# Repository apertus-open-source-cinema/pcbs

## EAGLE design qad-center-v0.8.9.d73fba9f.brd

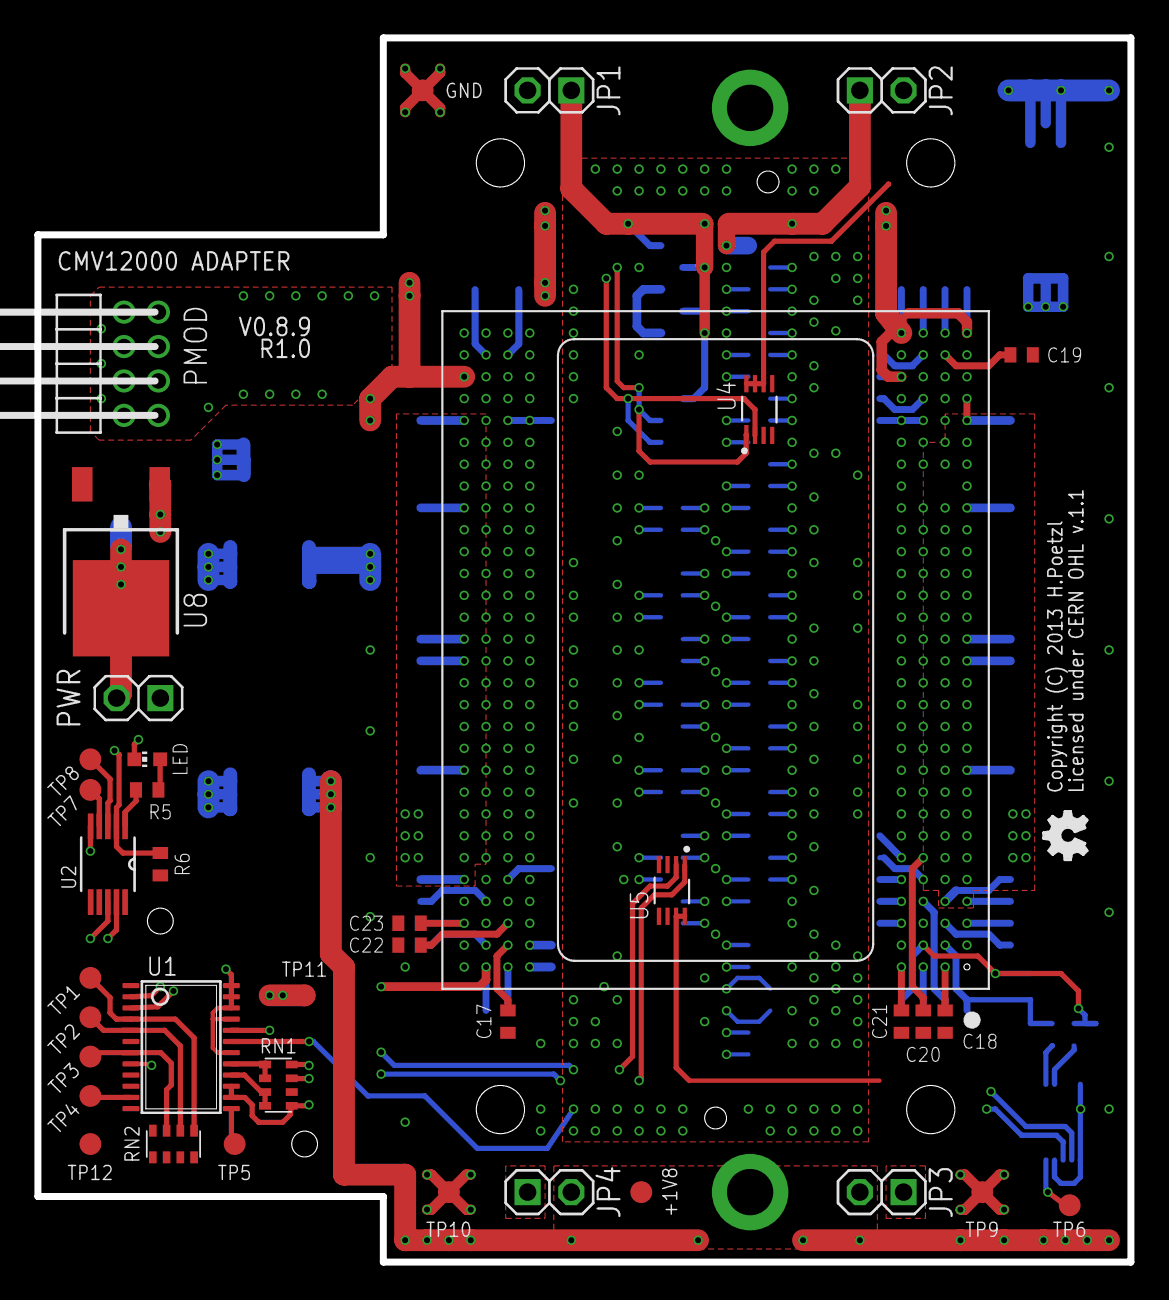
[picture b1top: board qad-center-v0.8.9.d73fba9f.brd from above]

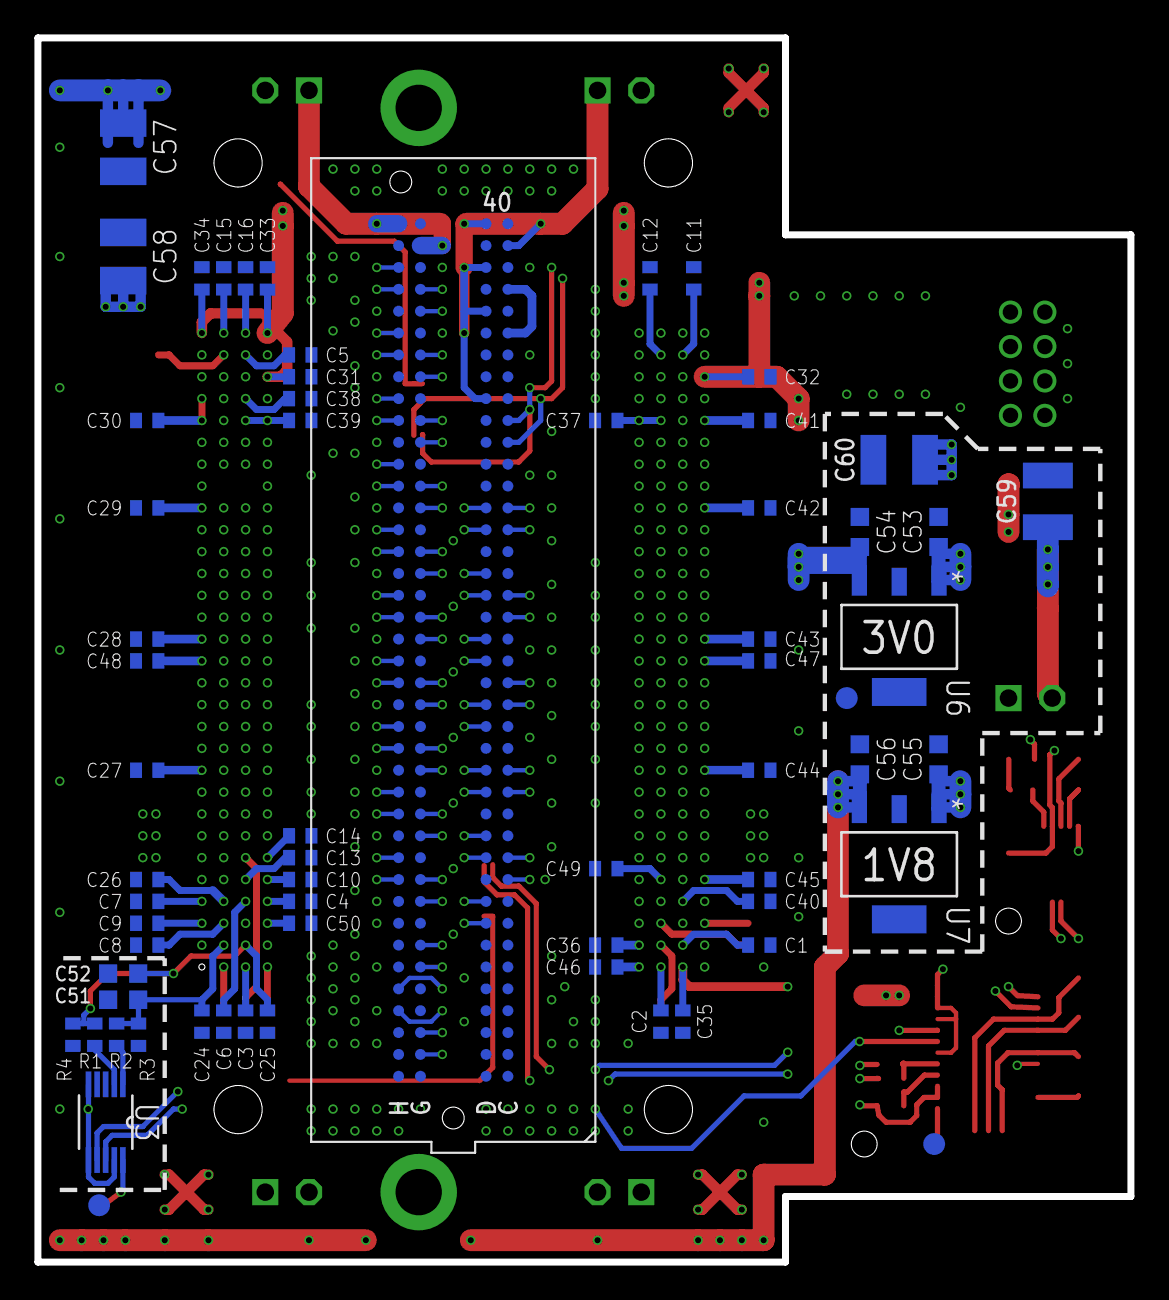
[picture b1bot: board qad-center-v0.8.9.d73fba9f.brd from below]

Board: 4 copper layers, 63.5 x 71.1 mm, 103 parts (63 on the bottom side), 130 nets.

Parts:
+1V8: TPB1,27; B1,27
C1, C2, C3, C4, C5, C6, C7, C8, C9, C10, C11, C12, C13, C14, C15, C16, C17, C18, C19, C20, C21, C22, C23, C24, C25, C26, C27, C28, C29, C30, C31, C32, C33, C34, C35, C36, C37, C38, C39, C40, C41, C42, C43, C44, C45, C46, C47, C48, C49, C50: 100n; C0402
C51, C52, C53, C54, C55, C56: 10u; C0603K
C57, C58: 100u; C1210
C59, C60: 100u; C1210K
GND: TPB1,27; B1,27
GND*1, GND*2, GND*3: TPB1,27; B1,27
JP1, JP2, JP3, JP4: 1X02-S
LED: RED; CHIP-LED0603
PMOD: PMOD-8; 2X04/90/2MM
PWR: 1X02-S
R1, R2: 1R; R0402
R3, R4: R0402
R5: 220R; R0402
R6: 10k; R0402
RN1, RN2: 10k; EXBV8V
TP1, TP2, TP3, TP4, TP5, TP6, TP7, TP8, TP9, TP10, TP11, TP12: TPB1,27; B1,27
U1: LM96080; TSSOP24
U2: PCA9537; TSSOP-10
U3: AD5647R; SOP50P490X110-10N
U4, U5: LM75BGD; SOT996-2/3
U6: MCP1826S-3002E/DB; SOT230P700X180-4N
U7: MCP1826S-1802E/DB; SOT230P700X180-4N
U8: AP1084TO252; TO252
U$1: CMV12000ANDON+LM; 10-30-07-237-400T4+LM
U$5: OSHW_FILLX100_NOTEXT
ZED1: FMC-LPC-ZED_NOCCZED; ASP-134604-01-ZED

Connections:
+1V8: +1V8.TP, C56.1, C57.1, JP2.2, JP3.2, JP4.2, U7.3
+1V8A: C26.1, C27.1, C28.1, C29.1, C30.1, C48.1, JP3.1, TP9.TP, U1.19, U$1.A10, U$1.A15, U$1.A16, U$1.A22, U$1.A26, U$1.A27, U$1.B4
+1V8B: C41.1, C42.1, C43.1, C44.1, C45.1, C46.1, C47.1, JP4.1, TP10.TP, U1.20, U$1.E1, U$1.H5, U$1.H10, U$1.H15, U$1.H16, U$1.H22, U$1.H26
+3V0: C31.1, C32.1, C33.1, C34.1, C35.1, C54.1, RN1.3, TP11.TP, U6.3, U$1.A30, U$1.D28, U$1.D30, U$1.G1, U$1.H28
+3V3: C17.1, C18.1, C19.1, C20.1, C21.1, C22.1, C23.1, C36.1, C37.1, C38.1, C39.1, C40.1, C49.1, C50.1, C53.1, C55.1, C58.1, C60.1, JP1.2, R6.1, RN1.2, RN2.2, RN2.3, RN2.4, TP12.TP, U1.1, U1.6, U1.9, U1.12, U2.6, U2.10, U3.5, U3.6, U3.9, U4.6, U4.7, U4.8, U5.7, U5.8, U6.1, U7.1, U8.2, U$1.C26, U$1.C27, U$1.D3, U$1.D26, U$1.E2, U$1.E26, U$1.F5, U$1.F26, U$1.G4
+5V: C59.1, PWR.2, U8.3
GND: C1.2, C2.2, C3.2, C4.2, C5.2, C6.2, C7.2, C8.2, C9.2, C10.2, C11.2, C12.2, C13.2, C14.2, C15.2, C16.2, C24.2, C25.2, C26.2, C27.2, C28.2, C29.2, C30.2, C31.2, C32.2, C33.2, C34.2, C35.2, C36.2, C37.2, C38.2, C39.2, C40.2, C41.2, C42.2, C43.2, C44.2, C45.2, C46.2, C47.2, C48.2, C49.2, C50.2, C51.2, C52.2, C53.2, C54.2, C55.2, C56.2, C57.2, C58.2, C59.2, C60.2, GND.TP, GND*1.TP, GND*2.TP, GND*3.TP, LED.C, PWR.1, R3.2, R4.2, RN1.1, RN1.4, U1.8, U1.14, U1.15, U1.18, U1.21, U1.22, U1.23, U1.24, U2.5, U3.3, U3.4, U4.4, U4.5, U5.4, U5.5, U5.6, U6.2, U6.4, U7.2, U7.4, U8.1, U$1.A9, U$1.A21, U$1.A25, U$1.A28, U$1.A29, U$1.B5, U$1.B22, U$1.B26, U$1.B27, U$1.B28, U$1.C15, U$1.C16, U$1.C28, U$1.D2, U$1.D25, U$1.D27, U$1.D29, U$1.E3, U$1.E15, U$1.E16, U$1.E25, U$1.E27, U$1.F27, U$1.G5, U$1.H1, U$1.H6, U$1.H9, U$1.H21, U$1.H25, U$1.H27, ZED1.C1, ZED1.C4, ZED1.C5, ZED1.C8, ZED1.C9, ZED1.C12, ZED1.C13, ZED1.C16, ZED1.C17, ZED1.C20, ZED1.C21, ZED1.C24, ZED1.C25, ZED1.C28, ZED1.C29, ZED1.C32, ZED1.C33, ZED1.C36, ZED1.C38, ZED1.C40, ZED1.D2, ZED1.D3, ZED1.D6, ZED1.D7, ZED1.D10, ZED1.D13, ZED1.D16, ZED1.D19, ZED1.D22, ZED1.D25, ZED1.D28, ZED1.D37, ZED1.D39, ZED1.G1, ZED1.G4, ZED1.G5, ZED1.G8, ZED1.G11, ZED1.G14, ZED1.G17, ZED1.G20, ZED1.G23, ZED1.G26, ZED1.G29, ZED1.G32, ZED1.G35, ZED1.G38, ZED1.G40, ZED1.H3, ZED1.H6, ZED1.H9, ZED1.H12, ZED1.H15, ZED1.H18, ZED1.H21, ZED1.H24, ZED1.H27, ZED1.H30, ZED1.H33, ZED1.H36, ZED1.H39
unnamed: C17.2, U$1.F2
unnamed: C18.2, U$1.B1
unnamed: C19.2, U$1.B29
unnamed: C20.2, U$1.C6
unnamed: C21.2, U$1.D1
unnamed: C22.2, U$1.F3
unnamed: C23.2, U$1.H3
unnamed: C1.1, U$1.G2
unnamed: C2.1, U$1.F1
unnamed: C3.1, U$1.C1
unnamed: C4.1, U$1.D4
unnamed: C5.1, U$1.C29
unnamed: C6.1, U$1.C4
unnamed: C7.1, U$1.A4
unnamed: C8.1, U$1.B3
unnamed: C9.1, U$1.A3
unnamed: C10.1, U$1.D5
unnamed: C11.1, U$1.G29
unnamed: C12.1, U$1.F29
unnamed: C13.1, U$1.C5
unnamed: C14.1, U$1.D6
unnamed: C15.1, U$1.B30
unnamed: C16.1, U$1.C30
unnamed: U$1.B6, ZED1.H11
unnamed: U$1.B7, ZED1.H10
unnamed: PMOD.1, U$1.F28
unnamed: U$1.D7, ZED1.D12
unnamed: U$1.D8, ZED1.D11
unnamed: PMOD.8, U$1.H29
unnamed: PMOD.2, U$1.E28
unnamed: PMOD.7, U$1.G28
unnamed: PMOD.10, U$1.E30
unnamed: PMOD.4, U$1.G30
unnamed: U$1.B8, ZED1.H14
unnamed: U$1.C9, ZED1.D15
unnamed: U$1.C10, ZED1.D14
unnamed: ZED1.C35, ZED1.C37
unnamed: JP1.1, ZED1.C39, ZED1.D32, ZED1.D36, ZED1.D38, ZED1.D40
unnamed: JP2.1, ZED1.G39, ZED1.H40
unnamed: R1.2, U3.2
unnamed: U$1.G10, ZED1.G13
unnamed: U$1.A11, ZED1.D18
unnamed: U$1.A12, ZED1.D17
unnamed: U$1.C11, ZED1.H17
unnamed: U$1.C12, ZED1.H16
unnamed: U$1.A13, ZED1.D21
unnamed: U$1.A14, ZED1.D20
unnamed: U$1.D13, ZED1.H20
unnamed: U$1.D14, ZED1.H19
unnamed: U$1.F16, ZED1.G22
unnamed: U$1.F17, ZED1.G21
unnamed: U$1.A17, ZED1.H26
unnamed: U$1.A18, ZED1.H25
unnamed: U$1.C17, ZED1.D24
unnamed: U$1.C18, ZED1.D23
unnamed: U$1.A19, ZED1.H29
unnamed: U$1.A20, ZED1.H28
unnamed: U$1.C19, ZED1.D27
unnamed: U$1.C20, ZED1.D26
unnamed: U$1.D21, ZED1.H32
unnamed: U$1.D22, ZED1.H31
unnamed: U$1.A23, ZED1.H35
unnamed: U$1.A24, ZED1.H34
unnamed: U$1.B24, ZED1.H38
unnamed: U$1.B25, ZED1.H37
unnamed: U$1.D15, ZED1.H23
unnamed: U$1.D16, ZED1.H22
unnamed: U$1.G22, ZED1.G34
unnamed: U$1.G23, ZED1.G33
unnamed: U$1.E22, ZED1.G30
unnamed: U$1.E21, ZED1.G31
unnamed: U$1.F21, ZED1.G27
unnamed: U$1.F20, ZED1.G28
unnamed: U$1.E20, ZED1.C26
unnamed: U$1.E19, ZED1.C27
unnamed: U$1.F19, ZED1.G24
unnamed: U$1.F18, ZED1.G25
unnamed: U$1.E18, ZED1.C22
unnamed: U$1.E17, ZED1.C23
unnamed: U$1.H23, ZED1.G37
unnamed: U$1.H24, ZED1.G36
unnamed: U$1.G15, ZED1.G18
unnamed: U$1.G14, ZED1.G19
unnamed: U$1.H14, ZED1.C18
unnamed: U$1.H13, ZED1.C19
unnamed: U$1.G13, ZED1.G15
unnamed: U$1.G12, ZED1.G16
unnamed: U$1.H12, ZED1.C14
unnamed: U$1.H11, ZED1.C15
unnamed: U$1.G11, ZED1.G12
unnamed: U$1.B9, ZED1.H13
unnamed: U$1.F9, ZED1.C10
unnamed: U$1.F8, ZED1.C11
unnamed: U$1.E8, ZED1.G9
unnamed: U$1.E7, ZED1.G10
unnamed: U$1.F7, ZED1.G6
unnamed: U$1.F6, ZED1.G7
unnamed: U$1.E5, ZED1.H5
unnamed: U$1.E6, ZED1.H4
unnamed: U$1.G6, ZED1.G3
unnamed: U$1.G7, ZED1.G2
unnamed: U$1.A5, ZED1.D9
unnamed: U$1.A6, ZED1.D8
unnamed: PMOD.9, U$1.H30
unnamed: PMOD.3, U$1.E29
unnamed: RN2.5, TP1.TP, U1.4
unnamed: R6.2, U2.2, U$1.F30
unnamed: R5.1, U2.1
unnamed: RN2.6, TP2.TP, U1.5
unnamed: TP8.TP, U2.3
unnamed: TP7.TP, U2.4
unnamed: RN1.5, RN1.6, U1.17
unnamed: RN2.7, TP3.TP, U1.7
unnamed: TP4.TP, U1.11
unnamed: TP5.TP, U1.13
unnamed: RN1.7, RN1.8, U1.16
unnamed: R2.2, U3.1
unnamed: LED.A, R5.2
unnamed: TP6.TP, U3.10
SCL: U1.3, U2.8, U3.7, U4.2, U5.2, ZED1.C30
SDA: U1.2, U2.9, U3.8, U4.1, U5.1, ZED1.C31
VTREF: C24.1, C51.1, R2.1, R3.1, U$1.B2
VTSIG: C25.1, C52.1, R1.1, R4.1, U$1.C2

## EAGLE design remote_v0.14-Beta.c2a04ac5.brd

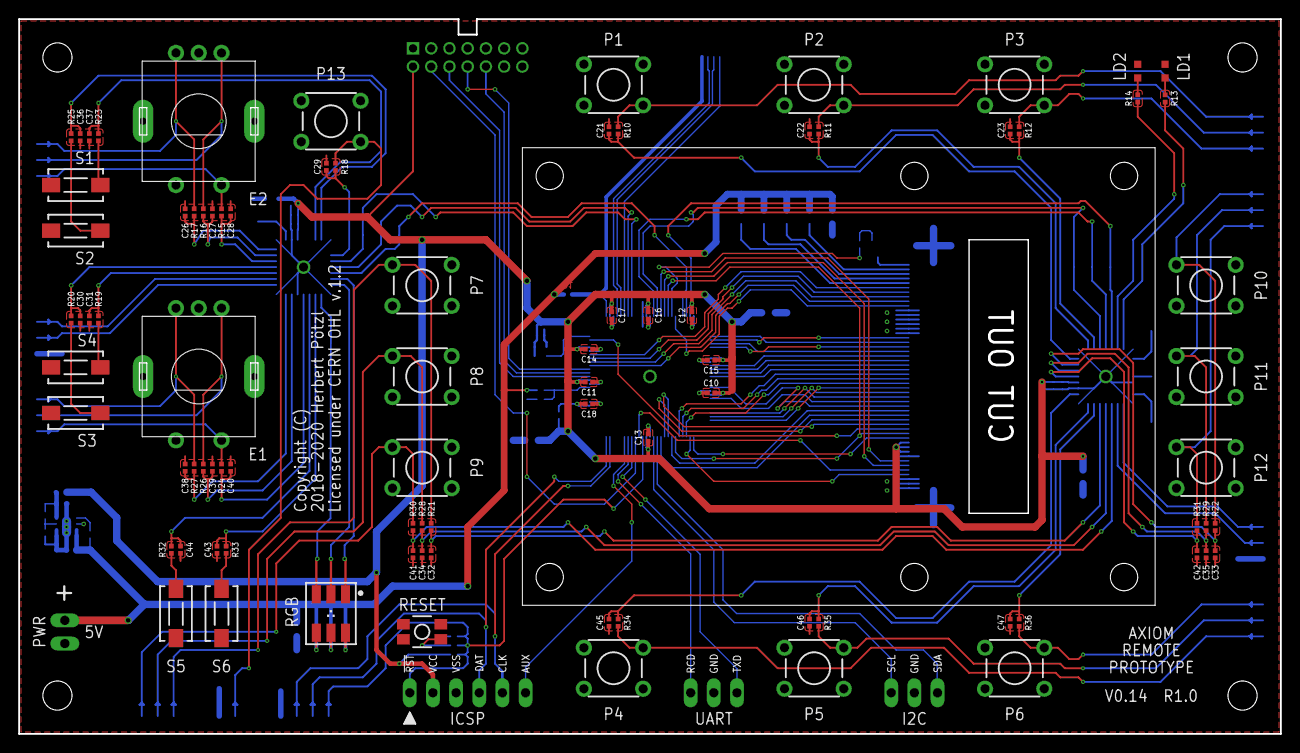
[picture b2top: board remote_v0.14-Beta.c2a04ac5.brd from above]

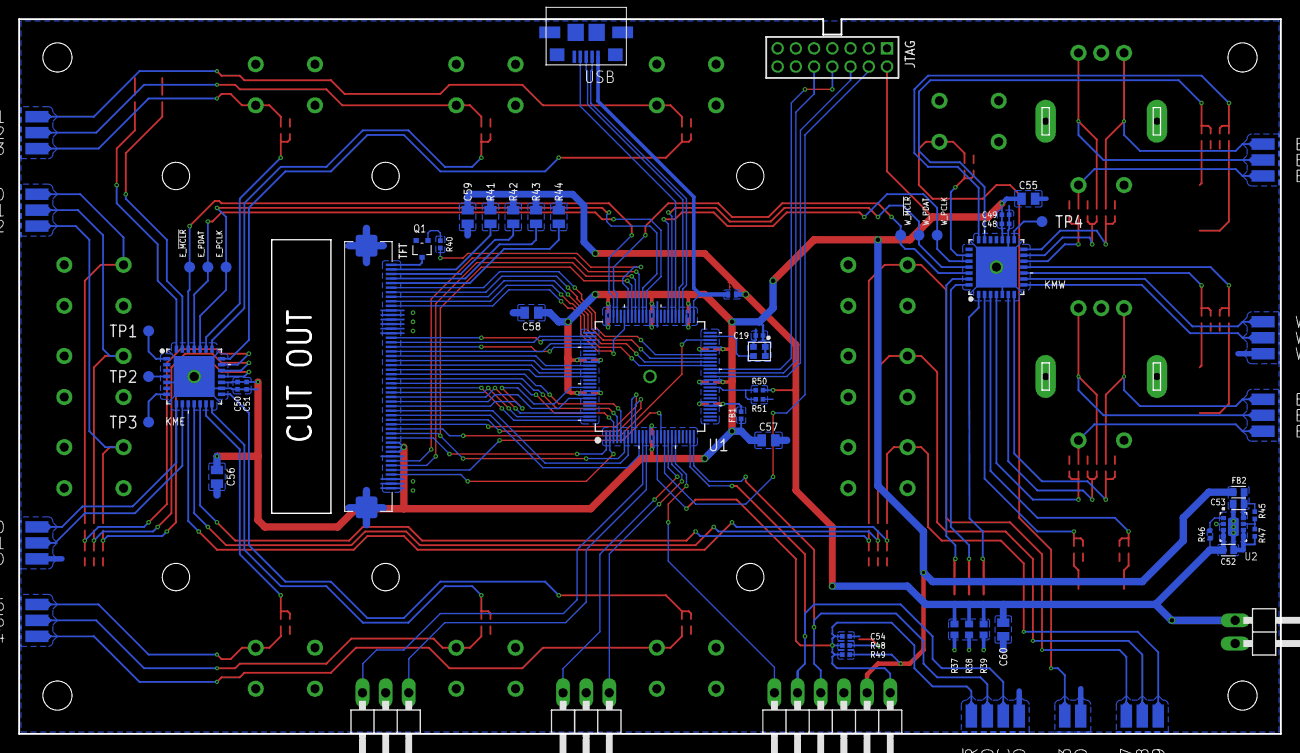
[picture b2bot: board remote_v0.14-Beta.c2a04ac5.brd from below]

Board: 2 copper layers, 138.4 x 78.4 mm, 171 parts (84 on the bottom side), 139 nets.

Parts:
!MCLR: 50X100-MIL
B_GND: 50X100-MIL
B_P1, B_P2, B_P3, B_P4, B_P5, B_P6, B_P7, B_P8, B_P9, B_P10, B_P11, B_P12, B_P13: 50X100-MIL
C10, C11, C12, C13, C14, C15, C16, C17, C18, C48, C50, C54: 100n; 0402-C
C19, C49, C51: 1u; 0402-C
C21, C22, C23, C26, C27, C28, C29, C30, C31, C32, C33, C34, C35, C36, C37, C38, C39, C40, C41, C42, C43, C44, C45, C46, C47: 0402-C
C52, C53: 10u; 0603-C
C55, C56, C57, C58, C59, C60: 22u; 0805-C
C_GND: 50X100-MIL
D1: PMEG2010BELD; DFN1006D-2
E1, E2: EC11_SW-LP
E1_A, E1_B, E1_S, E2_A, E2_B, E2_S: 50X100-MIL
E_!MCLR: TPTP12R; TP12R
E_GND: 50X100-MIL
E_PCLK: TPTP12R; TP12R
E_PDAT: TPTP12R; TP12R
E_RC0, E_RC1: 50X100-MIL
FB1: 600R; 0402-C
FB2: 33R; 0603-C
I2C: 1X03/90
ICSP: 1X06/90
JTAG: 2X07M
KME: PIC16F1718-I/ML; QFN65P600X600X100-29N
KMW: PIC16F1718-I/ML; QFN65P600X600X100-29N
LD1, LD2: LED; CHIPLED_0603
P1, P2, P3, P4, P5, P6, P7, P8, P9, P10, P11, P12, P13: DTSM-6THT; 6X6-THT
PGEC: 50X100-MIL
PGED: 50X100-MIL
PWR: 1X02/90
Q1: MMBT2222; SOT323
R10, R11, R12, R13, R14, R15, R16, R17, R18, R19, R20, R21, R22, R23, R24, R25, R26, R27, R28, R29, R30, R31, R32, R33, R34, R35, R36: 0402-C
R37, R38, R39: 0603-C
R40: 2k; 0402-C
R41, R42, R43, R44: 68R; 0805-C
R45: 510k; 0402-C
R46, R49, R50, R51: 10k; 0402-C
R47: 162k; 0402-C
R48: 1k; 0402-C
RESET: DTSM-6; 3X4MM
RGB: RGBLED_PLCC6
S1, S2, S3, S4, S5, S6: DTSM-3
TFT: TFT_2.83IN_240X320_50PIN
TP1, TP2, TP3, TP4: TPTP12R; TP12R
U1: PIC32MZ-100; QFP40P1200X1200X120-100N
U2: TPS82085; MICROSIP
U3: SMD-OSC-2.0X1.6; 2.0X1.6
UART: 1X03/90
USB: 5_USB_3S; MICRO-AB-H-SMT
W_!MCLR: TPTP12R; TP12R
W_GND: 50X100-MIL
W_PCLK: TPTP12R; TP12R
W_PDAT: TPTP12R; TP12R
W_RC0, W_RC1: 50X100-MIL

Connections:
3V3: C10.1, C11.1, C12.1, C13.1, C14.1, C15.1, C16.1, C17.1, C19.1, C48.1, C49.1, C50.1, C51.1, C55.1, C56.1, C57.1, C58.1, FB1.1, FB2.2, ICSP.2, JTAG.2, KME.17, KMW.17, R49.2, TFT.40, TFT.41, TFT.42, U1.14, U1.37, U1.46, U1.52, U1.62, U1.74, U1.83, U1.93, U3.1, U3.4
5V0: C52.1, C59.1, C60.1, D1.C, PWR.1, R37.1, R38.1, R39.1, R41.1, R42.1, R43.1, R44.1, R46.2, R50.2, U2.3, U2.4
!MCLR: !MCLR.1, C54.1, ICSP.1, R48.2, R49.1, U1.15
!SS6: TFT.38, U1.6, U1.68
AN6: R50.1, R51.2, U1.35
AVDD: C18.1, FB1.2, U1.30
B: KMW.27, RGB.1
D+: U1.55, USB.3
D-: U1.54, USB.2
E1_A: C39.1, KMW.6, R26.1
E1_B: C38.1, KMW.7, R27.1
E1_S: C40.1, KMW.4, R24.2
E2_A: C27.1, KMW.13, R16.1
E2_B: C26.1, KMW.14, R17.1
E2_S: C28.1, KMW.12, R15.2
EN_B: R46.1, U2.1
FB_B: R45.1, R47.2, U2.7
G: KMW.28, RGB.2
GND: B_GND.1, C10.2, C11.2, C12.2, C13.2, C14.2, C15.2, C16.2, C17.2, C18.2, C19.2, C21.2, C22.2, C23.2, C26.2, C27.2, C28.2, C29.2, C30.2, C31.2, C32.1, C33.1, C34.1, C35.1, C36.2, C37.2, C38.2, C39.2, C40.2, C41.1, C42.1, C43.2, C44.2, C45.1, C46.1, C47.1, C48.2, C49.2, C50.2, C51.2, C52.2, C53.2, C54.2, C55.2, C56.2, C57.2, C58.2, C59.2, C60.2, C_GND.1, E1.C, E1.E, E2.C, E2.E, E_GND.1, I2C.2, ICSP.3, JTAG.1, JTAG.3, JTAG.5, JTAG.7, JTAG.9, JTAG.11, JTAG.13, KME.5, KME.16, KME.EP, KMW.5, KMW.16, KMW.EP, LD1.C, LD2.C, P1.1, P2.1, P3.1, P4.3, P5.3, P6.3, P7.4, P8.4, P9.4, P10.4, P11.4, P12.4, P13.1, PWR.2, Q1.2, R47.1, R51.1, RESET.1, S1.1, S2.1, S3.1, S4.1, S5.1, S6.1, TFT.11, TFT.12, TFT.13, TFT.14, TFT.15, TFT.16, TFT.43, TFT.48, TFT.49, TFT.50, U1.13, U1.31, U1.36, U1.45, U1.53, U1.61, U1.63, U1.75, U1.84, U1.92, U2.5, U2.6, U2.EP, U3.2, UART.2, USB.5, USB.Z1, USB.Z2, USB.Z3, USB.Z4, USB.Z5, USB.Z6, W_GND.1
KME_!MCLR: E_!MCLR.TP, KME.26, U1.73
KME_PCLK: E_PCLK.TP, KME.24, U1.65
KME_PDAT: E_PDAT.TP, KME.25, U1.64
KMW_!MCLR: KMW.26, U1.72, W_!MCLR.TP
KMW_PCLK: KMW.24, U1.58, W_PCLK.TP
KMW_PDAT: KMW.25, U1.57, W_PDAT.TP
LED_A1: R41.2, TFT.2
LED_A2: R42.2, TFT.3
LED_A3: R43.2, TFT.4
LED_A4: R44.2, TFT.5
LED_CK: Q1.3, TFT.1
unnamed: E2.A, E2_A.1, R16.2
unnamed: B_P1.1, P1.4, R10.2
unnamed: E2.B, E2_B.1, R17.2
unnamed: B_P2.1, P2.4, R11.2
unnamed: B_P3.1, P3.4, R12.2
unnamed: E2.D, E2_S.1, R15.1
unnamed: R19.2, S3.2
unnamed: R20.2, S4.2
unnamed: R23.2, S1.2
unnamed: R25.2, S2.2
unnamed: LD1.A, R13.2
unnamed: LD2.A, R14.2
unnamed: E1.A, E1_A.1, R26.2
unnamed: E1.B, E1_B.1, R27.2
unnamed: E1.D, E1_S.1, R24.1
unnamed: R32.2, S5.2
unnamed: R33.2, S6.2
unnamed: B_P4.1, P4.2, R34.1
unnamed: B_P5.1, P5.2, R35.1
unnamed: B_P6.1, P6.2, R36.1
unnamed: B_P9.1, P9.1, R30.2
unnamed: B_P12.1, P12.1, R31.2
unnamed: B_P8.1, P8.1, R28.2
unnamed: B_P11.1, P11.1, R29.2
unnamed: B_P7.1, P7.1, R21.2
unnamed: B_P10.1, P10.1, R22.2
unnamed: KMW.9, W_RC1.1
unnamed: R39.2, RGB.4
unnamed: R38.2, RGB.5
unnamed: KME.1, TP1.TP
unnamed: KME.7, TP3.TP
unnamed: KME.4, TP2.TP
unnamed: R37.2, RGB.6
unnamed: B_P13.1, P13.4, R18.1
unnamed: KMW.15, TP4.TP
unnamed: R48.1, RESET.4
unnamed: Q1.1, R40.1
unnamed: E_RC0.1, KME.8
unnamed: E_RC1.1, KME.9
unnamed: KMW.8, W_RC0.1
OSC1: U1.49, U3.3
P1: C21.1, KME.21, R10.1
P2: C22.1, KME.22, R11.1
P3: C23.1, KME.23, R12.1
P4: C45.2, KME.15, R34.2
P5: C46.2, KME.14, R35.2
P6: C47.2, KME.13, R36.2
P7: C32.2, KME.12, R21.1
P8: C34.2, KME.11, R28.1
P9: C41.2, KME.10, R30.1
P10: C33.2, KME.20, R22.1
P11: C35.2, KME.19, R29.1
P12: C42.2, KME.18, R31.1
P13: C29.1, KMW.23, R18.2
PGEC1: ICSP.5, PGEC.1, U1.24
PGED1: ICSP.4, PGED.1, U1.25
PMD0: TFT.32, U1.91
PMD1: TFT.31, U1.94
PMD2: TFT.30, U1.98
PMD3: TFT.29, U1.99
PMD4: TFT.28, U1.100
PMD5: TFT.27, U1.3
PMD6: TFT.26, U1.4
PMD7: TFT.25, U1.5
PMD8: TFT.24, U1.88
PMD9: TFT.23, U1.87
PMD10: TFT.22, U1.86
PMD11: TFT.21, U1.85
PMD12: TFT.20, U1.79
PMD13: TFT.19, U1.80
PMD14: TFT.18, U1.77
PMD15: TFT.17, U1.78
PMRD: TFT.35, U1.9
PMWR: TFT.36, U1.8
R: KMW.1, RGB.3
RA5: TFT.47, U1.2
RB12: TFT.9, U1.41
RB13: TFT.8, U1.42
RG15: TFT.39, U1.1
RPB5: ICSP.6, U1.20
RPB14: TFT.7, U1.43
RPB15: TFT.6, U1.44
RPD10: R40.2, U1.69
RPD11: TFT.10, U1.70
RPE8: U1.18, UART.3
RPE9: U1.19, UART.1
RPG9: TFT.46, U1.16
S1_A: C44.1, KMW.3, R32.1
S1_B: C43.1, KMW.2, R33.1
S2_A: KME.28, R13.1
S2_B: KME.27, R14.1
SCK6: TFT.37, U1.48
SCL1: TFT.44, U1.66
SCL4: I2C.1, U1.12
SDA1: TFT.45, U1.67
SDA4: I2C.3, U1.11
SDI6: TFT.33, U1.7
SDO6: TFT.34, U1.10
TCK: JTAG.6, U1.38
TDI: JTAG.10, U1.39
TDO: JTAG.8, U1.40
TMS: JTAG.4, U1.17
TS1_A: C37.1, KMW.20, R23.1
TS1_B: C36.1, KMW.21, R25.1
TS2_A: C31.1, KMW.10, R19.1
TS2_B: C30.1, KMW.11, R20.1
USBID: U1.56, USB.4
VBUS: D1.A, U1.51, USB.1
VOUT_B: C53.1, FB2.1, R45.2, U2.8

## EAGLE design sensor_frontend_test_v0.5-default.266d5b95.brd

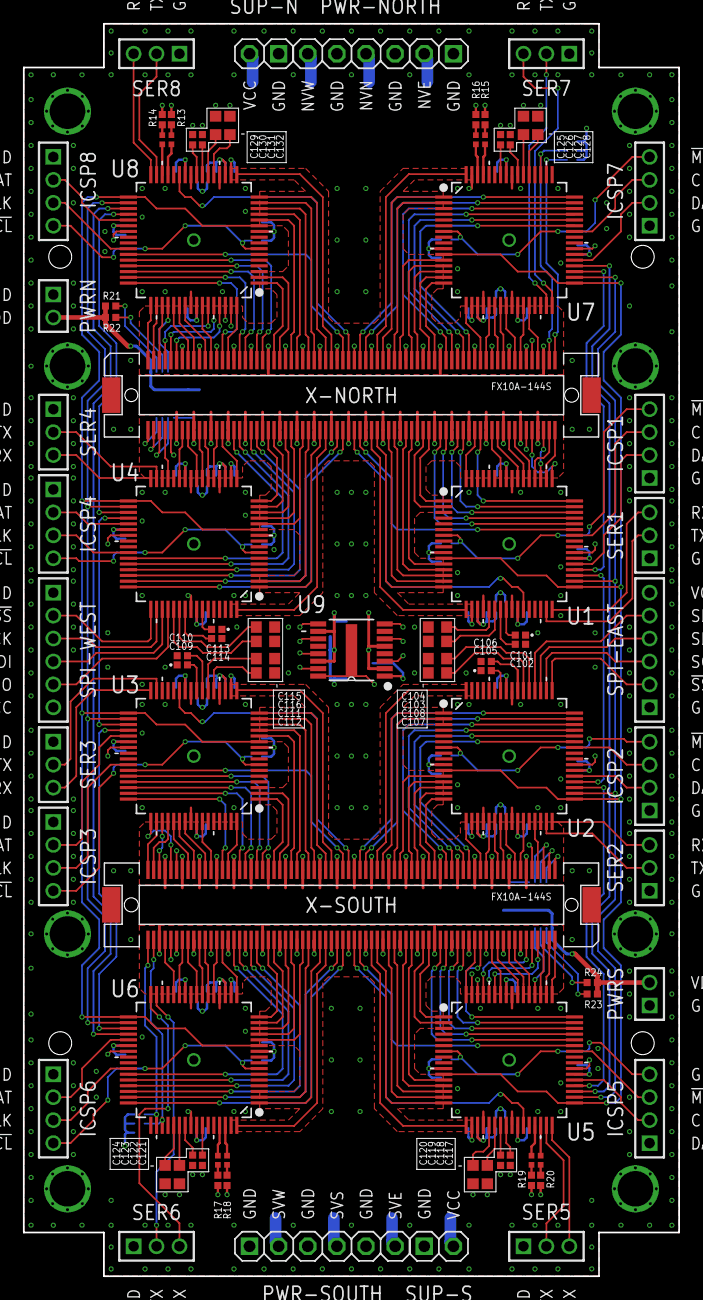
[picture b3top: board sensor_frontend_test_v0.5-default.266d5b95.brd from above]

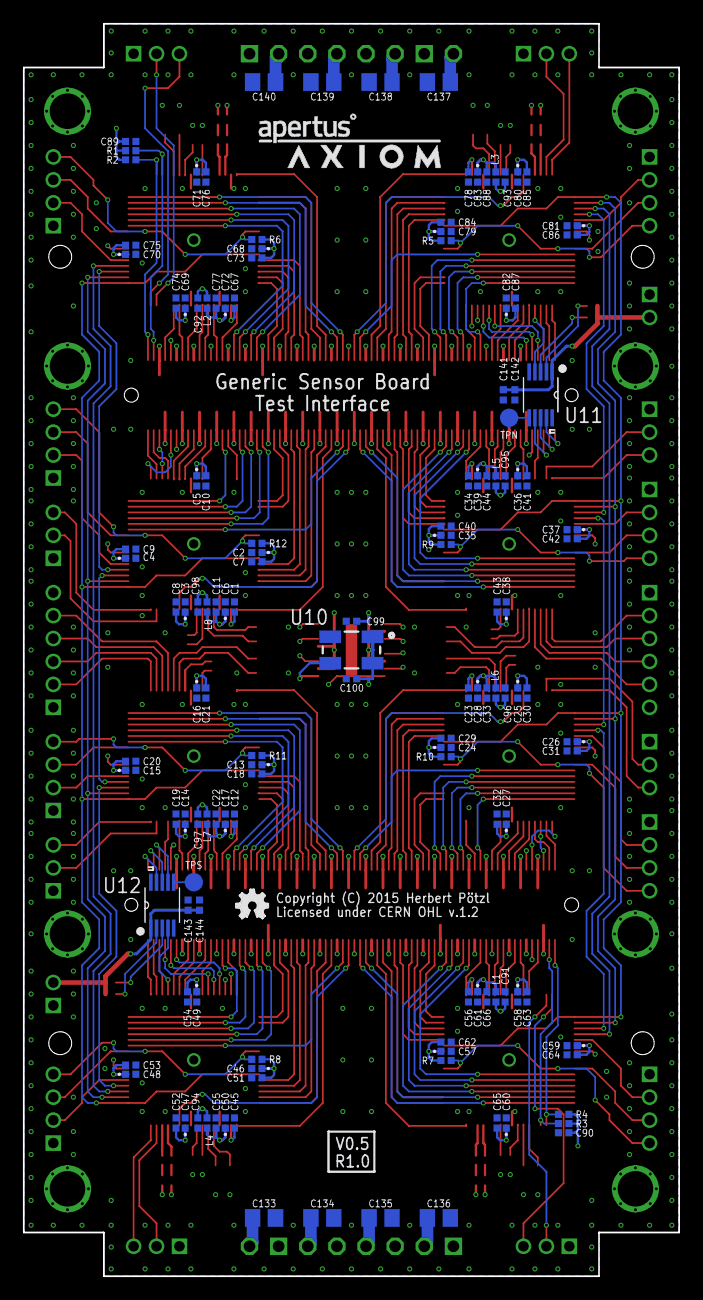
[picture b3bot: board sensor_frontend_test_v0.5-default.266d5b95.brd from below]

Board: 4 copper layers, 57.1 x 109.2 mm, 223 parts (140 on the bottom side), 345 nets.

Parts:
C1, C2, C3, C4, C5, C6, C7, C8, C9, C10, C11, C12, C13, C14, C15, C16, C17, C18, C19, C20, C21, C22, C23, C24, C25, C26, C27, C28, C29, C30, C31, C32, C33, C34, C35, C36, C37, C38, C39, C40, C41, C42, C43, C44, C45, C46, C47, C48, C49, C50, C51, C52, C53, C54, C55, C56, C57, C58, C59, C60, C61, C62, C63, C64, C65, C66, C67, C68, C69, C70, C71, C72, C73, C74, C75, C76, C77, C78, C79, C80, C81, C82, C83, C84, C85, C86, C87, C88, C89, C90, C91, C92, C93, C94, C95, C96, C97, C98, C99, C100, C101, C102, C105, C106, C109, C110, C113, C114, C117, C118, C121, C122, C125, C126, C129, C130, C141, C142, C143, C144: 0402-B
C103, C104, C107, C108, C111, C112, C115, C116, C119, C120, C123, C124, C127, C128, C131, C132: 0603-B
C133, C134, C135, C136, C137, C138, C139, C140: 0805-A
ICSP1, ICSP2, ICSP3, ICSP4, ICSP5, ICSP6, ICSP7, ICSP8: 1X04M
L1, L2, L3, L4, L5, L6, L7, L8: 0402-B
LED1, LED2, LED3, LED4: DUAL-LED-0404; 0404
LOGO1: OSHW_LOGO_FILLX0100-NT; OSHW_FILLX100_NOTEXT
PWR-NORTH: 1X06-S
PWR-SOUTH: 1X06-S
PWRN: 1X02M
PWRS: 1X02M
R1, R2, R3, R4, R5, R6, R7, R8, R9, R10, R11, R12, R13, R14, R15, R16, R17, R18, R19, R20, R21, R22, R23, R24: 0402-B
SER1, SER2, SER3, SER4, SER5, SER6, SER7, SER8: 1X03M
SPI-EAST: 1X06M
SPI-WEST: 1X06M
SUP-N: 1X02-S
SUP-S: 1X02-S
TPN: TPTP16R; TP16R
TPS: TPTP16R; TP16R
U1, U2, U3, U4, U5, U6, U7, U8: PIC16F1526-I/PT; QFP50P1200X1200X120-64N
U9: SI53365; SOP65P640X120-16N
U10: OSCILLATOR5X3-PIN1-INDICATED; CRYSTAL-OSC-SMD-5X3
U11, U12: MCP4728-E/UN; SOP50P490X110-10N
U$2: APERTUS_LOGO334X100; APERTUS_LOGO_334X100
U$3: AXIOM_LOGO525X80; AXIOM_LOGO_525X80
X-NORTH: FX10-144S; FX10A-144S
X-SOUTH: FX10-144S; FX10A-144S

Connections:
!E_SS: U1.11, U1.33, U2.11, U2.33, U5.11, U5.33, U7.11, U7.33
!LDAC_N: U8.52, U11.4
!LDAC_S: U5.52, U12.4
!MCLR1!: ICSP1.4, R12.2, U1.7
!MCLR2!: ICSP2.4, R11.2, U2.7
!MCLR3!: ICSP3.4, R10.2, U3.7
!MCLR4!: ICSP4.4, R9.2, U4.7
!MCLR5!: ICSP5.4, R8.2, U5.7
!MCLR6!: ICSP6.4, R7.2, U6.7
!MCLR7!: ICSP7.4, R6.2, U7.7
!MCLR8!: ICSP8.4, R5.2, U8.7
!W_SS: U3.11, U3.33, U4.11, U4.33, U6.11, U6.33, U8.11, U8.33
AVCC1: C6.1, C11.1, L8.2, U1.19
AVCC2: C17.1, C22.1, L7.2, U2.19
AVCC3: C28.1, C33.1, L6.2, U3.19
AVCC4: C39.1, C44.1, L5.2, U4.19
AVCC5: C50.1, C55.1, L4.2, U5.19
AVCC6: C61.1, C66.1, L1.2, U6.19
AVCC7: C72.1, C77.1, L2.2, U7.19
AVCC8: C83.1, C88.1, L3.2, U8.19
CAP1A: C101.1, U1.24
CAP1B: C102.1, U1.23
CAP1C: C103.1, U1.22
CAP1D: C104.1, U1.21
CAP2A: C105.1, U2.58
CAP2B: C106.1, U2.55
CAP2C: C107.1, U2.54
CAP2D: C108.1, U2.53
CAP3A: C109.1, U3.24
CAP3B: C110.1, U3.23
CAP3C: C111.1, U3.22
CAP3D: C112.1, U3.21
CAP4A: C113.1, U4.58
CAP4B: C114.1, U4.55
CAP4C: C115.1, U4.54
CAP4D: C116.1, U4.53
CAP5A: C117.1, U5.24
CAP5B: C118.1, U5.23
CAP5C: C119.1, U5.22
CAP5D: C120.1, U5.21
CAP6A: C121.1, U6.58
CAP6B: C122.1, U6.55
CAP6C: C123.1, U6.54
CAP6D: C124.1, U6.53
CAP7A: C125.1, U7.58
CAP7B: C126.1, U7.55
CAP7C: C127.1, U7.54
CAP7D: C128.1, U7.53
CAP8A: C129.1, U8.24
CAP8B: C130.1, U8.23
CAP8C: C131.1, U8.22
CAP8D: C132.1, U8.21
CLKIN1: U1.39, U9.8
CLKIN2: U2.39, U9.16
CLKIN3: U3.39, U9.15
CLKIN4: U4.39, U9.9
CLKIN5: U5.39, U9.3
CLKIN6: U6.39, U9.13
CLKIN7: U7.39, U9.6
CLKIN8: U8.39, U9.11
E_SCK: U1.34, U2.34, U5.34, U7.34
E_SD_17: U1.36, U7.35
E_SD_21: U1.35, U2.36
E_SD_52: U2.35, U5.36
E_SD_75: U5.35, U7.36
GND: C1.2, C2.2, C3.2, C4.2, C5.2, C6.2, C7.2, C8.2, C9.2, C10.2, C11.2, C12.2, C13.2, C14.2, C15.2, C16.2, C17.2, C18.2, C19.2, C20.2, C21.2, C22.2, C23.2, C24.2, C25.2, C26.2, C27.2, C28.2, C29.2, C30.2, C31.2, C32.2, C33.2, C34.2, C35.2, C36.2, C37.2, C38.2, C39.2, C40.2, C41.2, C42.2, C43.2, C44.2, C45.2, C46.2, C47.2, C48.2, C49.2, C50.2, C51.2, C52.2, C53.2, C54.2, C55.2, C56.2, C57.2, C58.2, C59.2, C60.2, C61.2, C62.2, C63.2, C64.2, C65.2, C66.2, C67.2, C68.2, C69.2, C70.2, C71.2, C72.2, C73.2, C74.2, C75.2, C76.2, C77.2, C78.2, C79.2, C80.2, C81.2, C82.2, C83.2, C84.2, C85.2, C86.2, C87.2, C88.2, C89.2, C90.2, C91.2, C92.2, C93.2, C94.2, C95.2, C96.2, C97.2, C98.2, C99.2, C100.2, C101.2, C102.2, C103.2, C104.2, C105.2, C106.2, C107.2, C108.2, C109.2, C110.2, C111.2, C112.2, C113.2, C114.2, C115.2, C116.2, C117.2, C118.2, C119.2, C120.2, C121.2, C122.2, C123.2, C124.2, C125.2, C126.2, C127.2, C128.2, C129.2, C130.2, C131.2, C132.2, C133.2, C134.2, C135.2, C136.2, C137.2, C138.2, C139.2, C140.2, C141.2, C142.2, C143.2, C144.2, ICSP1.1, ICSP2.1, ICSP3.1, ICSP4.1, ICSP5.1, ICSP6.1, ICSP7.1, ICSP8.1, PWR-NORTH.1, PWR-NORTH.3, PWR-NORTH.5, PWR-SOUTH.1, PWR-SOUTH.3, PWR-SOUTH.5, PWRN.1, PWRS.1, SER1.1, SER2.1, SER3.1, SER4.1, SER5.1, SER6.1, SER7.1, SER8.1, SPI-EAST.1, SPI-WEST.1, SUP-N.1, SUP-S.1, U1.9, U1.20, U1.25, U1.41, U1.56, U2.9, U2.20, U2.25, U2.41, U2.56, U3.9, U3.20, U3.25, U3.41, U3.56, U4.9, U4.20, U4.25, U4.41, U4.56, U5.9, U5.20, U5.25, U5.41, U5.56, U6.9, U6.20, U6.25, U6.41, U6.56, U7.9, U7.20, U7.25, U7.41, U7.56, U7.63, U8.9, U8.20, U8.25, U8.41, U8.56, U9.4, U9.7, U9.12, U10.2, U11.10, U12.10, X-NORTH.12, X-NORTH.18, X-NORTH.24, X-NORTH.30, X-NORTH.36, X-NORTH.42, X-NORTH.43, X-NORTH.48, X-NORTH.54, X-NORTH.60, X-NORTH.66, X-NORTH.72, X-NORTH.78, X-NORTH.84, X-NORTH.90, X-NORTH.96, X-NORTH.102, X-NORTH.103, X-NORTH.108, X-NORTH.114, X-NORTH.120, X-NORTH.126, X-NORTH.132, X-NORTH.138, X-NORTH.139, X-SOUTH.12, X-SOUTH.18, X-SOUTH.24, X-SOUTH.30, X-SOUTH.36, X-SOUTH.42, X-SOUTH.43, X-SOUTH.48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
ICSPCLK1: ICSP1.3, U1.42
ICSPCLK2: ICSP2.3, U2.42
ICSPCLK3: ICSP3.3, U3.42
ICSPCLK4: ICSP4.3, U4.42
ICSPCLK5: ICSP5.3, U5.42
ICSPCLK6: ICSP6.3, U6.42
ICSPCLK7: ICSP7.3, U7.42
ICSPCLK8: ICSP8.3, U8.42
ICSPDAT1: ICSP1.2, U1.37
ICSPDAT2: ICSP2.2, U2.37
ICSPDAT3: ICSP3.2, U3.37
ICSPDAT4: ICSP4.2, U4.37
ICSPDAT5: ICSP5.2, U5.37
ICSPDAT6: ICSP6.2, U6.37
ICSPDAT7: ICSP7.2, U7.37
ICSPDAT8: ICSP8.2, U8.37
LED5: LED4.4, U5.29
LED5B: LED4.3, U5.30
LED6: LED3.4, U6.61
LED6B: LED3.3, U6.62
LED7: LED2.4, U7.61
LED7B: LED2.3, U7.62
LED8: LED1.4, U8.29
LED8B: LED1.3, U8.30
N00_N: U4.24, X-NORTH.16
N00_P: U4.27, X-NORTH.14
N01_N: U8.54, X-NORTH.17
N01_P: U8.53, X-NORTH.15
N02_N: U4.22, X-NORTH.22
N02_P: U4.23, X-NORTH.20
N03_N: U8.58, X-NORTH.23
N03_P: U8.55, X-NORTH.21
N04_N: U4.17, X-NORTH.28
N04_P: U4.21, X-NORTH.26
N05_N: U8.64, X-NORTH.29
N05_P: U8.48, X-NORTH.27
N06_N: U4.44, X-NORTH.34
N06_P: U4.43, X-NORTH.32
N07_N: U8.46, X-NORTH.35
N07_P: U8.47, X-NORTH.33
N08_N: U4.46, X-NORTH.40
N08_P: U4.45, X-NORTH.38
N09_N: U8.44, X-NORTH.41
N09_P: U8.45, X-NORTH.39
N10_N: U4.15, X-NORTH.46
N10_P: U4.16, X-NORTH.44
N11_N: U8.2, X-NORTH.47
N11_P: U8.1, X-NORTH.45
N12_N: U4.13, X-NORTH.52
N12_P: U4.14, X-NORTH.50
N13_N: U8.13, X-NORTH.53
N13_P: U8.12, X-NORTH.51
N14_N: U4.2, X-NORTH.58
N14_P: U4.12, X-NORTH.56
N15_N: U8.15, X-NORTH.59
N15_P: U8.14, X-NORTH.57
N16_N: U4.64, X-NORTH.64
N16_P: U4.1, X-NORTH.62
N17_N: U8.17, X-NORTH.65
N17_P: U8.16, X-NORTH.63
N18_N: U4.48, X-NORTH.70
N18_P: U4.47, X-NORTH.68
N19_N: U8.27, X-NORTH.71
N19_P: U8.43, X-NORTH.69
N20_N: U1.43, X-NORTH.76
N20_P: U1.27, X-NORTH.74
N21_N: U7.47, X-NORTH.77
N21_P: U7.48, X-NORTH.75
N22_N: U1.16, X-NORTH.82
N22_P: U1.17, X-NORTH.80
N23_N: U7.1, X-NORTH.83
N23_P: U7.64, X-NORTH.81
N24_N: U1.14, X-NORTH.88
N24_P: U1.15, X-NORTH.86
N25_N: U7.12, X-NORTH.89
N25_P: U7.2, X-NORTH.87
N26_N: U1.12, X-NORTH.94
N26_P: U1.13, X-NORTH.92
N27_N: U7.14, X-NORTH.95
N27_P: U7.13, X-NORTH.93
N28_N: U1.1, X-NORTH.100
N28_P: U1.2, X-NORTH.98
N29_N: U7.16, X-NORTH.101
N29_P: U7.15, X-NORTH.99
N30_N: U1.45, X-NORTH.106
N30_P: U1.44, X-NORTH.104
N31_N: U7.45, X-NORTH.107
N31_P: U7.46, X-NORTH.105
N32_N: U1.47, X-NORTH.112
N32_P: U1.46, X-NORTH.110
N33_N: U7.43, X-NORTH.113
N33_P: U7.44, X-NORTH.111
N34_N: U1.48, X-NORTH.118
N34_P: U1.64, X-NORTH.116
N35_N: U7.21, X-NORTH.119
N35_P: U7.17, X-NORTH.117
N36_N: U1.55, X-NORTH.124
N36_P: U1.58, X-NORTH.122
N37_N: U7.23, X-NORTH.125
N37_P: U7.22, X-NORTH.123
N38_N: U1.53, X-NORTH.130
N38_P: U1.54, X-NORTH.128
N39_N: U7.27, X-NORTH.131
N39_P: U7.24, X-NORTH.129
unnamed: C45.1, U5.18
unnamed: U9.1, U10.3
unnamed: TPS.TP, U12.6
unnamed: C1.1, U1.18
unnamed: LED1.1, R13.2
unnamed: LED1.2, R14.2
unnamed: LED2.1, R15.2
unnamed: LED2.2, R16.2
unnamed: LED3.1, R17.2
unnamed: LED3.2, R18.2
unnamed: LED4.1, R19.2
unnamed: LED4.2, R20.2
unnamed: TPN.TP, U11.6
unnamed: C56.1, U6.18
unnamed: C12.1, U2.18
unnamed: C23.1, U3.18
unnamed: C34.1, U4.18
unnamed: C67.1, U7.18
unnamed: C78.1, U8.18
N_CHK_EN: U4.29, X-NORTH.8
N_CHK_V: C141.1, C142.1, PWRN.2, R21.1, R22.1, U11.1, X-NORTH.10
N_I2C_EN: U7.28, X-NORTH.137
N_SCK: U1.50, X-NORTH.144
N_SCL: R2.2, U7.50, X-NORTH.143
N_SDA: R1.2, U7.51, X-NORTH.141
N_SDI: U1.51, X-NORTH.140
N_SDO: U1.52, X-NORTH.142
N_SPI_EN: U1.49, X-NORTH.136
N_VE: C140.1, PWR-NORTH.2, X-NORTH.109, X-NORTH.115, X-NORTH.127, X-NORTH.133
N_VE_CV: U11.7, X-NORTH.6
N_VE_OV: U8.51, X-NORTH.5
N_VE_UV: U8.61, X-NORTH.11
N_VN: C139.1, PWR-NORTH.4, X-NORTH.49, X-NORTH.55, X-NORTH.61, X-NORTH.67, X-NORTH.79, X-NORTH.85, X-NORTH.91, X-NORTH.97
N_VN_CV: U11.8, X-NORTH.4
N_VN_OV: U8.50, X-NORTH.3
N_VN_UV: U8.60, X-NORTH.9
N_VW: C138.1, PWR-NORTH.6, X-NORTH.13, X-NORTH.19, X-NORTH.31, X-NORTH.37
N_VW_CV: U11.9, X-NORTH.2
N_VW_OV: U8.49, X-NORTH.1
N_VW_UV: U8.59, X-NORTH.7
RX1: SER1.3, U1.32
RX2: SER2.3, U2.32
RX3: SER3.3, U3.32
RX4: SER4.3, U4.32
RX5: SER5.3, U5.32
RX6: SER6.3, U6.32
RX7: SER7.3, U7.32
RX8: SER8.3, U8.32
S00_N: U2.24, X-SOUTH.16
S00_P: U2.27, X-SOUTH.14
S01_N: U5.54, X-SOUTH.17
S01_P: U5.53, X-SOUTH.15
S02_N: U2.22, X-SOUTH.22
S02_P: U2.23, X-SOUTH.20
S03_N: U5.58, X-SOUTH.23
S03_P: U5.55, X-SOUTH.21
S04_N: U2.17, X-SOUTH.28
S04_P: U2.21, X-SOUTH.26
S05_N: U5.64, X-SOUTH.29
S05_P: U5.48, X-SOUTH.27
S06_N: U2.44, X-SOUTH.34
S06_P: U2.43, X-SOUTH.32
S07_N: U5.46, X-SOUTH.35
S07_P: U5.47, X-SOUTH.33
S08_N: U2.46, X-SOUTH.40
S08_P: U2.45, X-SOUTH.38
S09_N: U5.44, X-SOUTH.41
S09_P: U5.45, X-SOUTH.39
S10_N: U2.15, X-SOUTH.46
S10_P: U2.16, X-SOUTH.44
S11_N: U5.2, X-SOUTH.47
S11_P: U5.1, X-SOUTH.45
S12_N: U2.13, X-SOUTH.52
S12_P: U2.14, X-SOUTH.50
S13_N: U5.13, X-SOUTH.53
S13_P: U5.12, X-SOUTH.51
S14_N: U2.2, X-SOUTH.58
S14_P: U2.12, X-SOUTH.56
S15_N: U5.15, X-SOUTH.59
S15_P: U5.14, X-SOUTH.57
S16_N: U2.64, X-SOUTH.64
S16_P: U2.1, X-SOUTH.62
S17_N: U5.17, X-SOUTH.65
S17_P: U5.16, X-SOUTH.63
S18_N: U2.48, X-SOUTH.70
S18_P: U2.47, X-SOUTH.68
S19_N: U5.27, X-SOUTH.71
S19_P: U5.43, X-SOUTH.69
S20_N: U3.43, X-SOUTH.76
S20_P: U3.27, X-SOUTH.74
S21_N: U6.47, X-SOUTH.77
S21_P: U6.48, X-SOUTH.75
S22_N: U3.16, X-SOUTH.82
S22_P: U3.17, X-SOUTH.80
S23_N: U6.1, X-SOUTH.83
S23_P: U6.64, X-SOUTH.81
S24_N: U3.14, X-SOUTH.88
S24_P: U3.15, X-SOUTH.86
S25_N: U6.12, X-SOUTH.89
S25_P: U6.2, X-SOUTH.87
S26_N: U3.12, X-SOUTH.94
S26_P: U3.13, X-SOUTH.92
S27_N: U6.14, X-SOUTH.95
S27_P: U6.13, X-SOUTH.93
S28_N: U3.1, X-SOUTH.100
S28_P: U3.2, X-SOUTH.98
S29_N: U6.16, X-SOUTH.101
S29_P: U6.15, X-SOUTH.99
S30_N: U3.45, X-SOUTH.106
S30_P: U3.44, X-SOUTH.104
S31_N: U6.45, X-SOUTH.107
S31_P: U6.46, X-SOUTH.105
S32_N: U3.47, X-SOUTH.112
S32_P: U3.46, X-SOUTH.110
S33_N: U6.43, X-SOUTH.113
S33_P: U6.44, X-SOUTH.111
S34_N: U3.48, X-SOUTH.118
S34_P: U3.64, X-SOUTH.116
S35_N: U6.21, X-SOUTH.119
S35_P: U6.17, X-SOUTH.117
S36_N: U3.55, X-SOUTH.124
S36_P: U3.58, X-SOUTH.122
S37_N: U6.23, X-SOUTH.125
S37_P: U6.22, X-SOUTH.123
S38_N: U3.53, X-SOUTH.130
S38_P: U3.54, X-SOUTH.128
S39_N: U6.27, X-SOUTH.131
S39_P: U6.24, X-SOUTH.129
SCK2B: SPI-EAST.3, U2.50
SCK4B: SPI-WEST.3, U4.50
SCL_N: R21.2, U8.63, U11.2
SCL_S: R23.2, U5.63, U12.2
SDA_N: R22.2, U8.62, U11.3
SDA_S: R24.2, U5.62, U12.3
SDI2B: SPI-EAST.4, U2.51
SDI4B: SPI-WEST.4, U4.51
SDO2B: SPI-EAST.5, U2.52
SDO4B: SPI-WEST.5, U4.52
SS2B: SPI-EAST.2, U2.49
SS4B: SPI-WEST.2, U4.49
S_CHK_EN: U2.29, X-SOUTH.8
S_CHK_V: C143.1, C144.1, PWRS.2, R23.1, R24.1, U12.1, X-SOUTH.10
S_I2C_EN: U6.28, X-SOUTH.137
S_SCK: U3.50, X-SOUTH.144
S_SCL: R4.2, U6.50, X-SOUTH.143
S_SDA: R3.2, U6.51, X-SOUTH.141
S_SDI: U3.51, X-SOUTH.140
S_SDO: U3.52, X-SOUTH.142
S_SPI_EN: U3.49, X-SOUTH.136
S_VE: C134.1, PWR-SOUTH.6, X-SOUTH.13, X-SOUTH.19, X-SOUTH.31, X-SOUTH.37
S_VE_CV: U12.9, X-SOUTH.2
S_VE_OV: U5.49, X-SOUTH.1
S_VE_UV: U5.59, X-SOUTH.7
S_VS: C135.1, PWR-SOUTH.4, X-SOUTH.49, X-SOUTH.55, X-SOUTH.61, X-SOUTH.67, X-SOUTH.79, X-SOUTH.85, X-SOUTH.91, X-SOUTH.97
S_VS_CV: U12.8, X-SOUTH.4
S_VS_OV: U5.50, X-SOUTH.3
S_VS_UV: U5.60, X-SOUTH.9
S_VW: C136.1, PWR-SOUTH.2, X-SOUTH.109, X-SOUTH.115, X-SOUTH.127, X-SOUTH.133
S_VW_CV: U12.7, X-SOUTH.6
S_VW_OV: U5.51, X-SOUTH.5
S_VW_UV: U5.61, X-SOUTH.11
TX1: SER1.2, U1.31
TX2: SER2.2, U2.31
TX3: SER3.2, U3.31
TX4: SER4.2, U4.31
TX5: SER5.2, U5.31
TX6: SER6.2, U6.31
TX7: SER7.2, U7.31
TX8: SER8.2, U8.31
VCC: C2.1, C3.1, C4.1, C5.1, C7.1, C8.1, C9.1, C10.1, C13.1, C14.1, C15.1, C16.1, C18.1, C19.1, C20.1, C21.1, C24.1, C25.1, C26.1, C27.1, C29.1, C30.1, C31.1, C32.1, C35.1, C36.1, C37.1, C38.1, C40.1, C41.1, C42.1, C43.1, C46.1, C47.1, C48.1, C49.1, C51.1, C52.1, C53.1, C54.1, C57.1, C58.1, C59.1, C60.1, C62.1, C63.1, C64.1, C65.1, C68.1, C69.1, C70.1, C71.1, C73.1, C74.1, C75.1, C76.1, C79.1, C80.1, C81.1, C82.1, C84.1, C85.1, C86.1, C87.1, C89.1, C90.1, C91.1, C92.1, C93.1, C94.1, C95.1, C96.1, C97.1, C98.1, C99.1, C100.1, C133.1, C137.1, L1.1, L2.1, L3.1, L4.1, L5.1, L6.1, L7.1, L8.1, R1.1, R2.1, R3.1, R4.1, R5.1, R6.1, R7.1, R8.1, R9.1, R10.1, R11.1, R12.1, R13.1, R14.1, R15.1, R16.1, R17.1, R18.1, R19.1, R20.1, SPI-EAST.6, SPI-WEST.6, SUP-N.2, SUP-S.2, U1.10, U1.26, U1.38, U1.57, U2.10, U2.26, U2.38, U2.57, U3.10, U3.26, U3.38, U3.57, U4.10, U4.26, U4.38, U4.57, U5.10, U5.26, U5.38, U5.57, U6.10, U6.26, U6.38, U6.57, U7.10, U7.26, U7.38, U7.57, U8.10, U8.26, U8.38, U8.57, U9.2, U9.5, U9.10, U9.14, U10.1, U10.4
W_SCK: U3.34, U4.34, U6.34, U8.34
W_SD_36: U3.36, U6.35
W_SD_43: U3.35, U4.36
W_SD_68: U6.36, U8.35
W_SD_84: U4.35, U8.36

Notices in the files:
qad-center-v0.8.9.d73fba9f.brd:
Copyright (C) 2013 H.Poetzl
Licensed under CERN OHL v.1.1
remote_v0.14-Beta.c2a04ac5.brd:
Copyright (C)
Licensed under CERN OHL v.1.2
sensor_frontend_test_v0.5-default.266d5b95.brd:
Copyright (C) 2015 Herbert Pötzl
parts and their libraries:
SparkFun-FreqCtrl: Licensing: CC v3.0 Share-Alike You are welcome to use this library for commercial purposes.
